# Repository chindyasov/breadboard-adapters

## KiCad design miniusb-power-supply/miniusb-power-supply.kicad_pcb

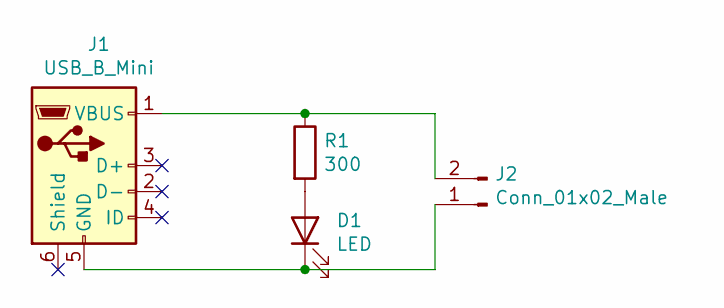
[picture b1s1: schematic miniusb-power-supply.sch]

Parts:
D1: LED; LED_D5.0mm
J1: USB_B_Mini; USB_Mini-B_Lumberg_2486_01_Horizontal
J2: Conn_01x02_Male; PinHeader_1x02_P2.54mm_Vertical
R1: 300; R_Axial_DIN0207_L6.3mm_D2.5mm_P7.62mm_Horizontal

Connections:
unnamed: D1.1 (K), J1.5 (GND), J2.1
unnamed: D1.2 (A), R1.2
unnamed: J1.1 (VBUS), J2.2, R1.1

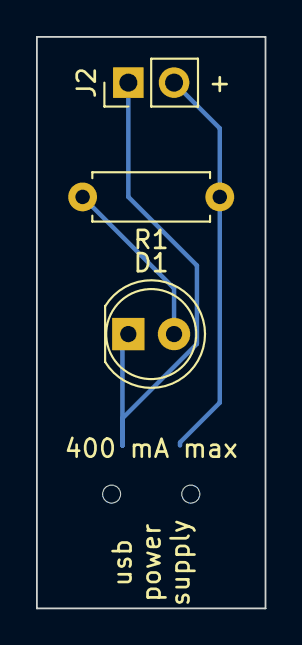
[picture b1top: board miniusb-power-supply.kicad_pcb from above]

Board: 2 copper layers, 12.7 x 31.8 mm, 4 parts (1 on the bottom side), 3 nets.

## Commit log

2021-07-20 Initialize repo
2021-07-20 Add SOT-223 project with complete electric schema
2021-07-20 Add SOT-223 PCB layout
2021-12-21 Add zones to SOT-223 PCB
2021-12-21 Add miniusb-power-supply project
2021-12-22 Add miniusb-power-supply schema and PCB layout
